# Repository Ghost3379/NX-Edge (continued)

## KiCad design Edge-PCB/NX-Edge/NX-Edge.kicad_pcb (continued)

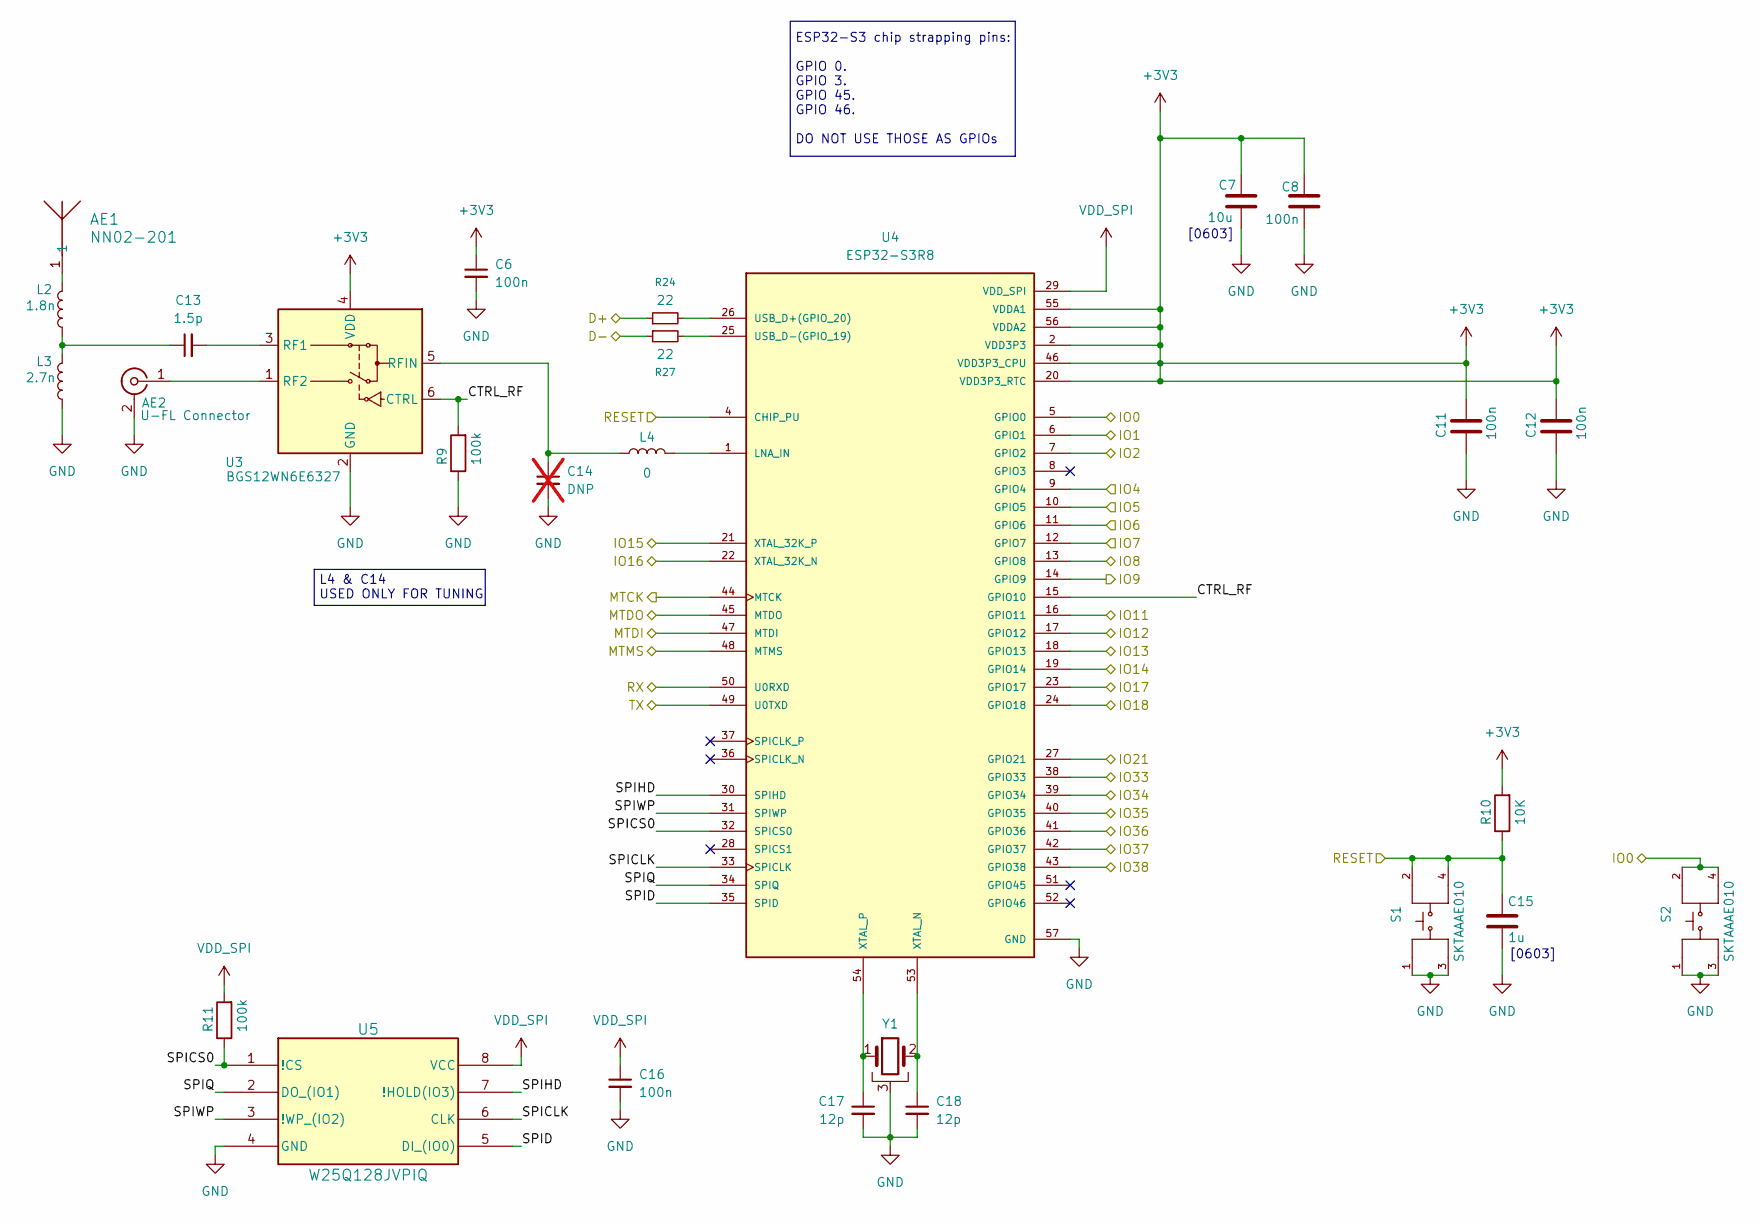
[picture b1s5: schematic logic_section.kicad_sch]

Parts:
AE1: NN02-201; ANT_NN02-201_IGN
AE2: U-FL Connector; U.FL_Hirose_U.FL-R-SMT-1_Vertical
C6, C8, C11, C12, C16: 100n; C_0402_1005Metric
C7: 10u; C_0603_1608Metric
C13: 1.5p; C_0402_1005Metric; Tolerance +-0.05pF
C14: DNP; C_0402_1005Metric; not fitted
C15: 1u; C_0603_1608Metric
C17, C18: 12p; C_0402_1005Metric
L2: 1.8n; L_0402_1005Metric; Tolerances +-0.1nH
L3: 2.7n; L_0402_1005Metric; Tolerances +-0.1nH
L4: 0; L_0402_1005Metric
R9, R11: 100k; R_0402_1005Metric
R10: 10K; R_0402_1005Metric
R24, R27: 22; R_0402_1005Metric
S1, S2: SKTAAAE010; KEY-SMD_4P-L2.6-W1.6-P0.80-LS3.0; LCSC C358616
U3: BGS12WN6E6327; Infineon_PG-TSNP-6-10_0.7x1.1mm_0.7x1.1mm_P0.4mm
U4: ESP32-S3R8; QFN40P700X700X90-57N; MPN ESP32-S3R8
U5: W25Q128JVPIQ; WSON_128JVPIQ_WIN
Y1: 40MHz; Crystal_SMD_2016-4Pin_2.0x1.6mm; Toleranc +- 1ppm

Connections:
+3V3: C6.1, C7.1, C8.1, C11.1, C12.1, R10.2, U3.4 (VDD), U4.2 (VDD3P3), U4.3 (VDD3P3), U4.20 (VDD3P3_RTC), U4.46 (VDD3P3_CPU), U4.55 (VDDA1), U4.56 (VDDA2); also elsewhere on the board
/Connections/CTRL_NP: U4.17 (GPIO12); also elsewhere on the board
/Connections/D+: R24.1; also elsewhere on the board
/Connections/D-: R27.1; also elsewhere on the board
/Connections/IO0: S2.2, S2.4, U4.5 (GPIO0); also elsewhere on the board
/Connections/IO1: U4.6 (GPIO1); also elsewhere on the board
/Connections/IO8: U4.13 (GPIO8); also elsewhere on the board
/Connections/IO9: U4.14 (GPIO9); also elsewhere on the board
/Connections/IO11: U4.16 (GPIO11); also elsewhere on the board
/Connections/IO14: U4.19 (GPIO14); also elsewhere on the board
/Connections/IO15: U4.21 (XTAL_32K_P); also elsewhere on the board
/Connections/IO16: U4.22 (XTAL_32K_N); also elsewhere on the board
/Connections/IO17: U4.23 (GPIO17); also elsewhere on the board
/Connections/IO18: U4.24 (GPIO18); also elsewhere on the board
/Connections/IO36: U4.41 (GPIO36); also elsewhere on the board
/Connections/IO37: U4.42 (GPIO37); also elsewhere on the board
/Connections/RST: C15.1, R10.1, S1.2, S1.4, U4.4 (CHIP_PU); also elsewhere on the board
/Connections/RX: U4.50 (U0RXD); also elsewhere on the board
/Connections/TX: U4.49 (U0TXD); also elsewhere on the board
/Logic section/CTRL_RF: R9.2, U3.6 (CTRL), U4.15 (GPIO10)
/Logic section/IO2: U4.7 (GPIO2); also elsewhere on the board
/Logic section/IO4: U4.9 (GPIO4); also elsewhere on the board
/Logic section/IO5: U4.10 (GPIO5); also elsewhere on the board
/Logic section/IO6: U4.11 (GPIO6); also elsewhere on the board
/Logic section/IO7: U4.12 (GPIO7); also elsewhere on the board
/Logic section/IO13: U4.18 (GPIO13); also elsewhere on the board
/Logic section/IO21: U4.27 (GPIO21); also elsewhere on the board
/Logic section/IO33: U4.38 (GPIO33); also elsewhere on the board
/Logic section/IO34: U4.39 (GPIO34); also elsewhere on the board
/Logic section/IO35: U4.40 (GPIO35); also elsewhere on the board
/Logic section/IO38: U4.43 (GPIO38); also elsewhere on the board
/Logic section/MTCK: U4.44 (MTCK); also elsewhere on the board
/Logic section/MTDI: U4.47 (MTDI); also elsewhere on the board
/Logic section/MTDO: U4.45 (MTDO); also elsewhere on the board
/Logic section/MTMS: U4.48 (MTMS); also elsewhere on the board
/Logic section/SPICLK: U4.33 (SPICLK), U5.6 (CLK)
/Logic section/SPICS0: R11.1, U4.32 (SPICS0), U5.1 (!CS)
/Logic section/SPID: U4.35 (SPID), U5.5 (DI_(IO0))
/Logic section/SPIHD: U4.30 (SPIHD), U5.7 (!HOLD(IO3))
/Logic section/SPIQ: U4.34 (SPIQ), U5.2 (DO_(IO1))
/Logic section/SPIWP: U4.31 (SPIWP), U5.3 (!WP_(IO2))
GND: AE2.2 (Ext), C6.2, C7.2, C8.2, C11.2, C12.2, C14.2, C15.2, C16.2, C17.2, C18.2, L3.1, R9.1, S1.1, S1.3, S2.1, S2.3, U3.2 (GND), U4.57 (GND), U5.4 (GND), Y1.3; also elsewhere on the board
unnamed: AE1.1 (1_1), L2.2
unnamed: AE2.1 (In), U3.1 (RF2)
unnamed: C13.1, L2.1, L3.2
unnamed: C13.2, U3.3 (RF1)
unnamed: C14.1, L4.1, U3.5 (RFIN)
unnamed: L4.2, U4.1 (LNA_IN)
unnamed: R24.2, U4.26 (USB_D+(GPIO_20))
unnamed: R27.2, U4.25 (USB_D-(GPIO_19))
unnamed: C18.1, U4.53 (XTAL_N), Y1.2
unnamed: C17.1, U4.54 (XTAL_P), Y1.1
VDD_SPI: C16.1, R11.2, U4.29 (VDD_SPI), U5.8 (VCC)

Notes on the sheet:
L4 & C14 USED ONLY FOR TUNING
[0603]
ESP32-S3 chip strapping pins: GPIO 0. GPIO 3. GPIO 45. GPIO 46. DO NOT USE THOSE AS GPIOs

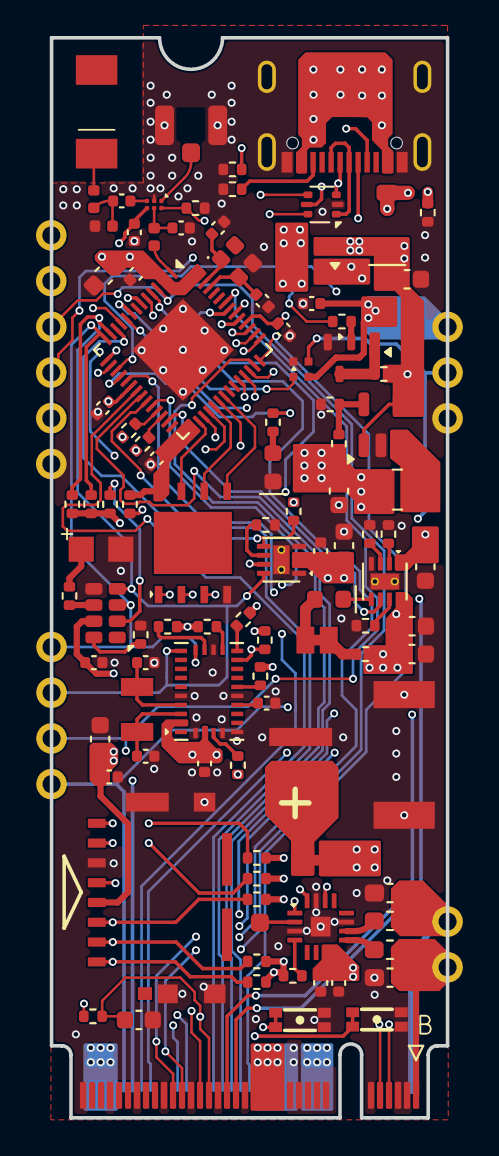
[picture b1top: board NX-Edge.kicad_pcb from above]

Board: 6 copper layers, 22.0 x 60.0 mm, 108 parts (0 on the bottom side), 92 nets.

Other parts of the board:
XYZ: n/a; XYZ_DOF_symbol

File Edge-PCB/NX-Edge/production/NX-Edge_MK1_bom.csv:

Designator,Footprint,Quantity,Value,LCSC Part #
AE1,ANT_NN02-201_IGN,1,NN02-201,
AE2,U.FL_Hirose_U.FL-R-SMT-1_Vertical,1,U-FL Connector,
"C1, C15, C2, C22",0603,4,1u,
"C11, C12, C16, C19, C21, C23, C24, C25, C26, C27, C30, C6, C8",0402,13,100n,
C13,0402,1,1.5p,
"C17, C18",0402,2,12p,
"C20, C3, C5, C7",0603,4,10u,
"C28, C29",0603,2,220pF,
"C31, C32",0402,2,22p,
C34,CAPCP3225X100N,1,CPH3225A,
C4,0603,1,4.7u,
D1,0603,1,ORANGE,
D2,D_SOD-123,1,NRVB230LSFT1G,
D3,0603,1,BLUE,
J1,105162-0001_MOL,1,1051620001,
J2,PinHeader_1x02_P2.54mm_Vertical,1,AUDIO_OUT,
J3,SAMESKY_UJ20-C-H-G-SMT-1-P16-TR,1,UJ20-C-H-G-SMT-1-P16-TR,
J5,PinHeader_1x04_P2.54mm_Vertical,1,BOTTOM,
J7,PinHeader_1x03_P2.54mm_Vertical,1,Ext. NeoPixel,
J8,M.2_2260-xx-B,1,Bus_M.2_Socket_B,
J9,PinHeader_1x06_P2.54mm_Vertical,1,TOP,
L1,1008,1,1u,
L2,0402,1,1.8n,
L3,0402,1,2.7n,
L4,0402,1,0,
"L5, L6",0603,2,Ferrite,
P1,JST_S2B-PH-SM4-TB,1,S2B-PH-SM4-TB,
"Q1, Q2",SOT-23,2,DMP3130L-7,
Q3,SOT-323_SC-70,1,BC847W,
"R1, R13, R8",0402,3,1k,
"R10, R14, R15, R16, R17, R18, R19, R7",0402,8,10K,
"R11, R12, R5, R6, R9",0402,5,100k,
R2,0402,1,27k,
"R20, R21",0402,2,5.1k,
"R23, R28, R29, R30, R31, R32, R33, R34, R36, R37",0402,10,4k7,
"R24, R27",0402,2,22,
R3,0402,1,499,
R35,0402,1,680k,
R4,0402,1,453k,
"S1, S2",KEY-SMD_4P-L2.6-W1.6-P0.80-LS3.0,2,SKTAAAE010,C358616
TH1,0402,1,10k NTC,
TP1,SolderWirePad_1x01_SMD_1x2mm,1,GAIN,
U1,SON50P200X200X80-9N,1,BQ25170DSGR,
U10,IC_BNO085,1,BNO085,
U11,SOT-666,1,USBLC6-2P6,
U2,SOT-23-5,1,TLV62569DBV,
U3,Infineon_PG-TSNP-6-10_0.7x1.1mm_0.7x1.1mm_P0.4mm,1,BGS12WN6E6327,
U4,QFN40P700X700X90-57N,1,ESP32-S3R8,ESP32-S3R8
U5,WSON_128JVPIQ_WIN,1,W25Q128JVPIQ,
U6,SON50P200X200X80-9N,1,MAX17048G_T10,
U7,MicroCrystal_C7_SON-8_1.5x3.2mm_P0.9mm,1,RV-3028-C7,
U8,LED-SMD_4P-L1.0-W1.0-TL_XL-1010RGBC-WS2812B,1,XL-1010RGBC-WS2812B,C5349953
U9,QFN50P300X300X80-17N,1,MAX98357AETE_T,
XYZ,XYZ_DOF_symbol,1,n/a,
Y1,Crystal_SMD_2016-4Pin_2.0x1.6mm,1,40MHz,
Y2,Crystal_SMD_3215-2Pin_3.2x1.5mm,1,32.768 kHz,
